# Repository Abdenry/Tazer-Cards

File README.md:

# [Tazer Cards](https://youtu.be/0fpzKOLWwhQ?si=C4kyu5y1s3HWvBQp)
A small device I made to convert the theoretical damage taken in popular card games into tangible outcomes. It uses an Arduino Nano, a modified TENS machine, a custom health tracker written in python, and cheap spark gap generators off ebay.
This was not built with scalability in mind as it was just a whim of the moment build to play with friends, as a result it is currnetly limited to two players only.

Improvements could be made by enabling more than two players but that would also require more hardware as the TENS machine can only accomodate two players. An automatic connection detector as the Arduino Nano changes COMM port everyone once and a while which requires updating the python health tracker.

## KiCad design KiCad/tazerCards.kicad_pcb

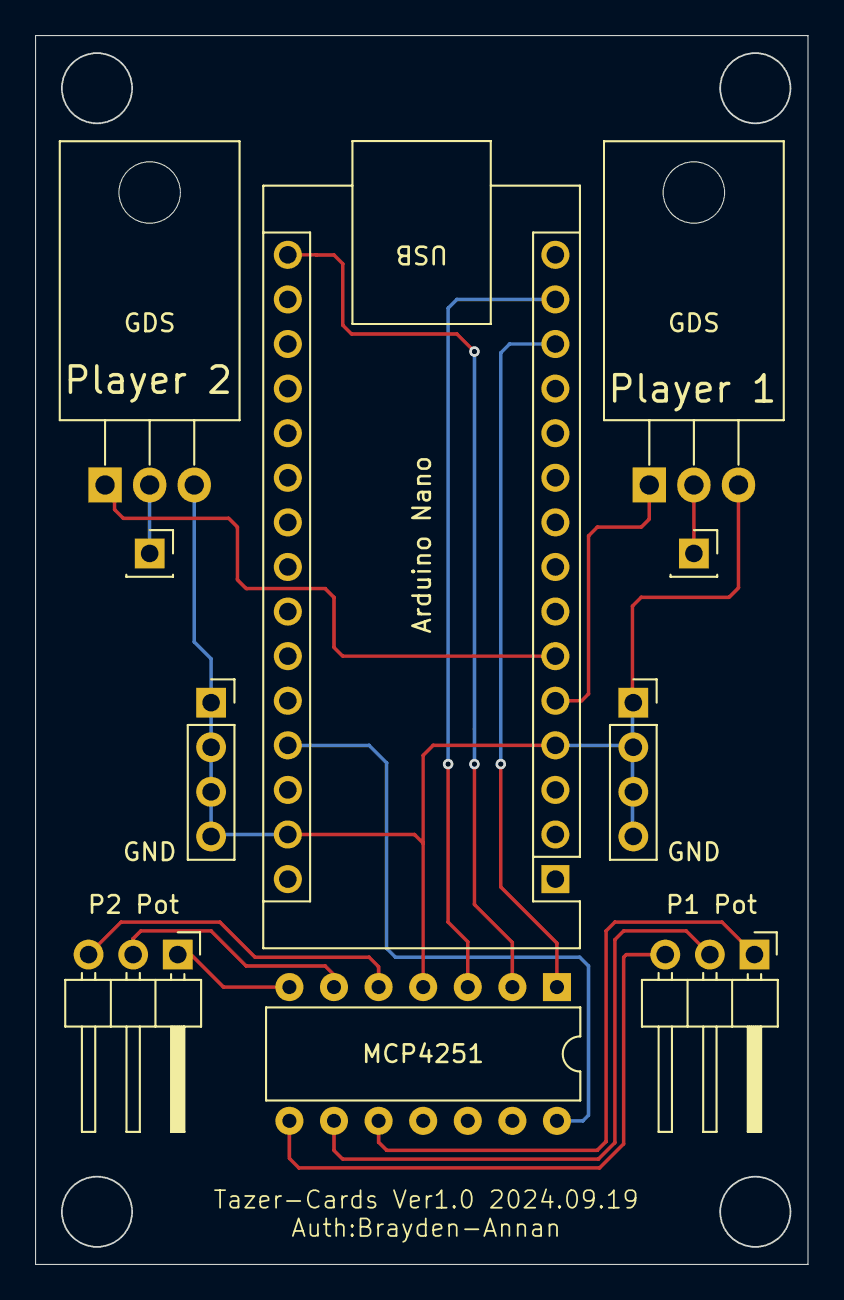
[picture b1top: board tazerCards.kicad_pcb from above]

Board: 2 copper layers, 44.0 x 69.9 mm, 10 parts (0 on the bottom side), 15 nets.

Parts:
A2: Arduino Nano; Arduino_Nano
J1: MCP4251; DIP-14_W7.62mm
J2, J6: SparkGapNegative; PinSocket_1x01_P2.54mm_Vertical
J3, J7: GND; PinSocket_1x04_P2.54mm_Vertical
J4: P2 Pot; PinHeader_1x03_P2.54mm_Horizontal
J5: P1 Pot; PinHeader_1x03_P2.54mm_Horizontal
Q1, Q2: GDS; TO-220-3_Horizontal_TabDown

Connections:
5V: A2.27 (+5V), J1.14
D2: A2.5 (D2), Q1.1 (G)
D3: A2.6 (D3), Q2.1 (G)
D10: A2.13 (D10), J1.1
D11: A2.14 (D11), J1.3
D13: A2.16 (D13), J1.2
GND: A2.4 (GND), A2.29 (GND), J1.4, J3.1, J3.2, J3.3, J3.4, J7.1, J7.2, J7.3, J7.4, Q1.3 (S), Q2.3 (S)
MCP5: J1.5, J4.3
MCP6: J1.6, J4.2
MCP7: J1.7, J4.1
MCP8: J1.8, J5.3
MCP9: J1.9, J5.2
MCP10: J1.10, J5.1
unnamed: J2.1, Q1.2 (D)
unnamed: J6.1, Q2.2 (D)

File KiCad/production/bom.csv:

Designator,Footprint,Quantity,Value,LCSC Part #
A2,Arduino_Nano,1,Arduino Nano,
J1,DIP-14_W7.62mm,1,MCP4251,
"J2, J6",PinSocket_1x01_P2.54mm_Vertical,2,SparkGapNegative,
"J3, J7",PinSocket_1x04_P2.54mm_Vertical,2,GND,
J4,PinHeader_1x03_P2.54mm_Horizontal,1,P2 Pot,
J5,PinHeader_1x03_P2.54mm_Horizontal,1,P1 Pot,
"Q1, Q2",TO-220-3_Horizontal_TabDown,2,GDS,

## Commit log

2024-10-08 Python Code for Health Tracker
    By no means a perfect implementation but it did its job.
2024-10-08 Arduino Code for Controlling Tazers
    Used for communication and controlling the output power of the tens unit and spark gap generator.
2024-10-08 moved python code to its own folder
2024-10-13 Added CAD files for project
